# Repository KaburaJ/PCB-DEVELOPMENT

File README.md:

# RELAY DRIVER SCHEMATIC AND PCB DEVELOPMENT

This project recreates a relay module that can be interphased with Arduino microcontroller and used to light a lamp.

## Problem Statement

The aim of this project is to contribute, though partially, to the problem of lack of the right components during electrical product design. Rather than a project coming to a stand still due to improper equipment, this project is proof that one can indeed make their own components from scratch- provided that the components required are readily available.

---
## Definitions

A `relay module` comprises of a transistor, diode, resistor and relay. The transistor, diode and resistor make up the `relay driver`.
A `relay` is an electromagnetic switch that is activated by little amounts of current and can be used to regulate much greater amounts of current. In this case, a `transistor` is used as an amplifier to the current from the power source(9V battery) that is used to energise the relay coil. The `resistor` ensures that a constant supply of 0.7V reaches the transistor to activate it. Consequently, the `diode` ensures that, when the circuit is switched OFF, there is no backflow of current to the transistor. 

---
## Implementation
This was done by KiCad software. The following are the schematic and 3D views of the PCB respectively.

---

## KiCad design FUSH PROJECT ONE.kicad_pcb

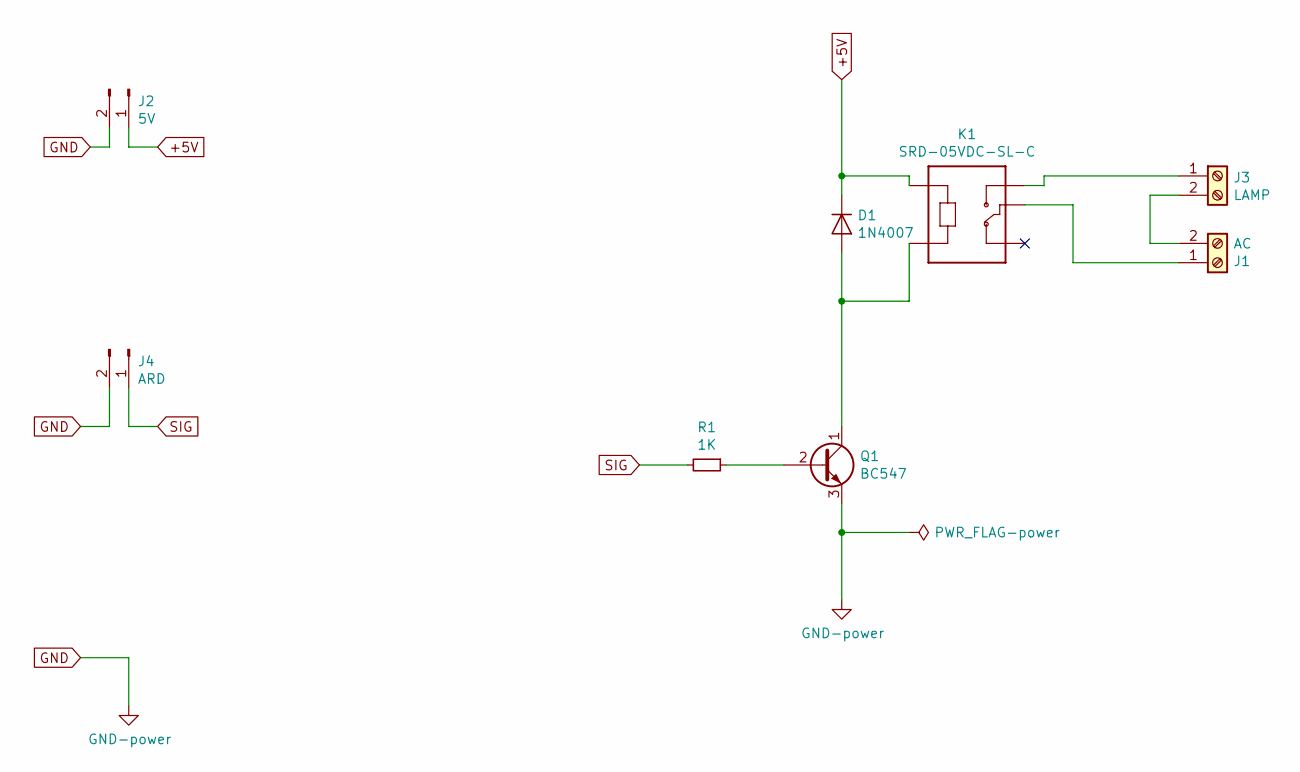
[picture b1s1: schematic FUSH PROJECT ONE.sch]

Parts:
D1: 1N4007; D_DO-41_SOD81_P12.70mm_Horizontal
J1: AC; TerminalBlock_Altech_AK300-2_P5.00mm
J2: 5V; PinHeader_1x02_P2.54mm_Vertical
J3: LAMP; TerminalBlock_Altech_AK300-2_P5.00mm
J4: ARD; PinHeader_1x02_P2.54mm_Vertical
K1: SRD-05VDC-SL-C; RELAY_SRD-05VDC-SL-C
Q1: BC547; TO-92_Inline
R1: 1K; R_Axial_DIN0207_L6.3mm_D2.5mm_P10.16mm_Horizontal

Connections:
+5V: D1.1 (K), J2.1, K1.A1
-5V: J2.2, J4.2, Q1.3 (E)
NO: J3.1, K1.NO
unnamed: D1.2 (A), K1.A2, Q1.1 (C)
unnamed: J1.1, K1.COM
unnamed: J1.2, J3.2
unnamed: J4.1, R1.2
unnamed: Q1.2 (B), R1.1

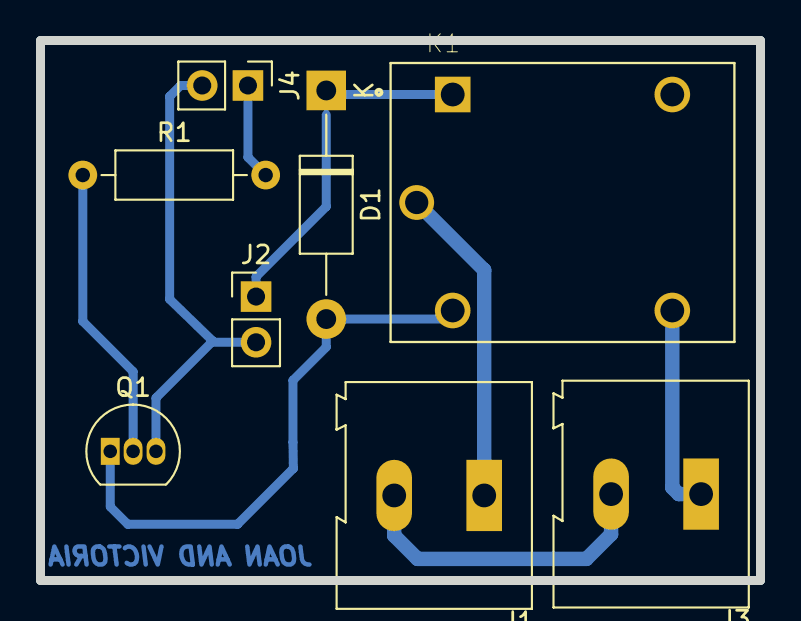
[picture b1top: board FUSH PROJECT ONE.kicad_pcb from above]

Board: 2 copper layers, 40.0 x 30.0 mm, 8 parts (0 on the bottom side), 8 nets.

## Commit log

2022-04-11 My First PCB
2022-04-14 Updated terminal labels
